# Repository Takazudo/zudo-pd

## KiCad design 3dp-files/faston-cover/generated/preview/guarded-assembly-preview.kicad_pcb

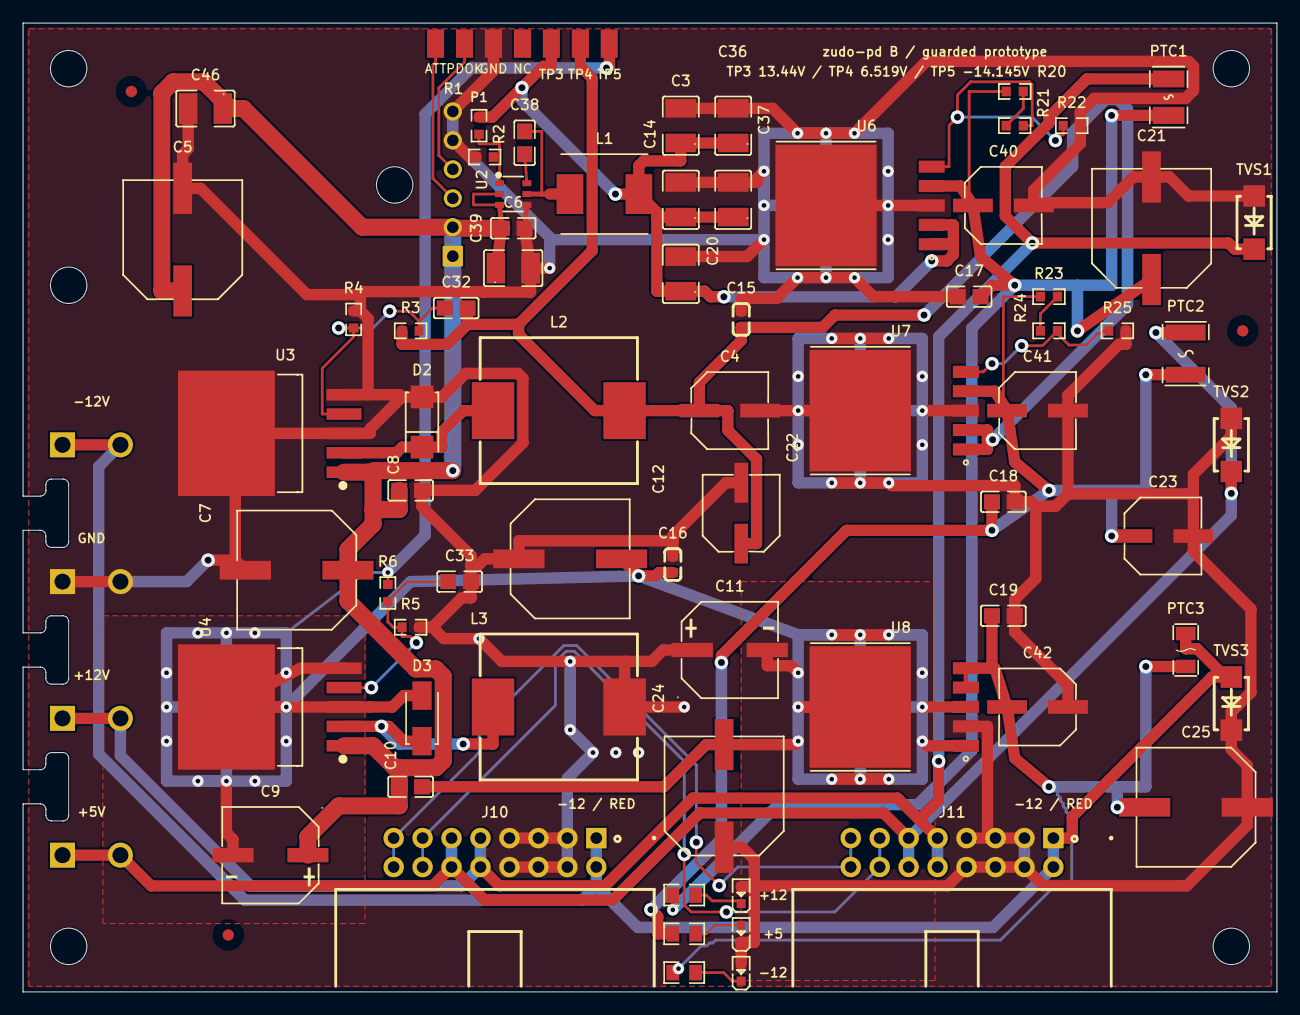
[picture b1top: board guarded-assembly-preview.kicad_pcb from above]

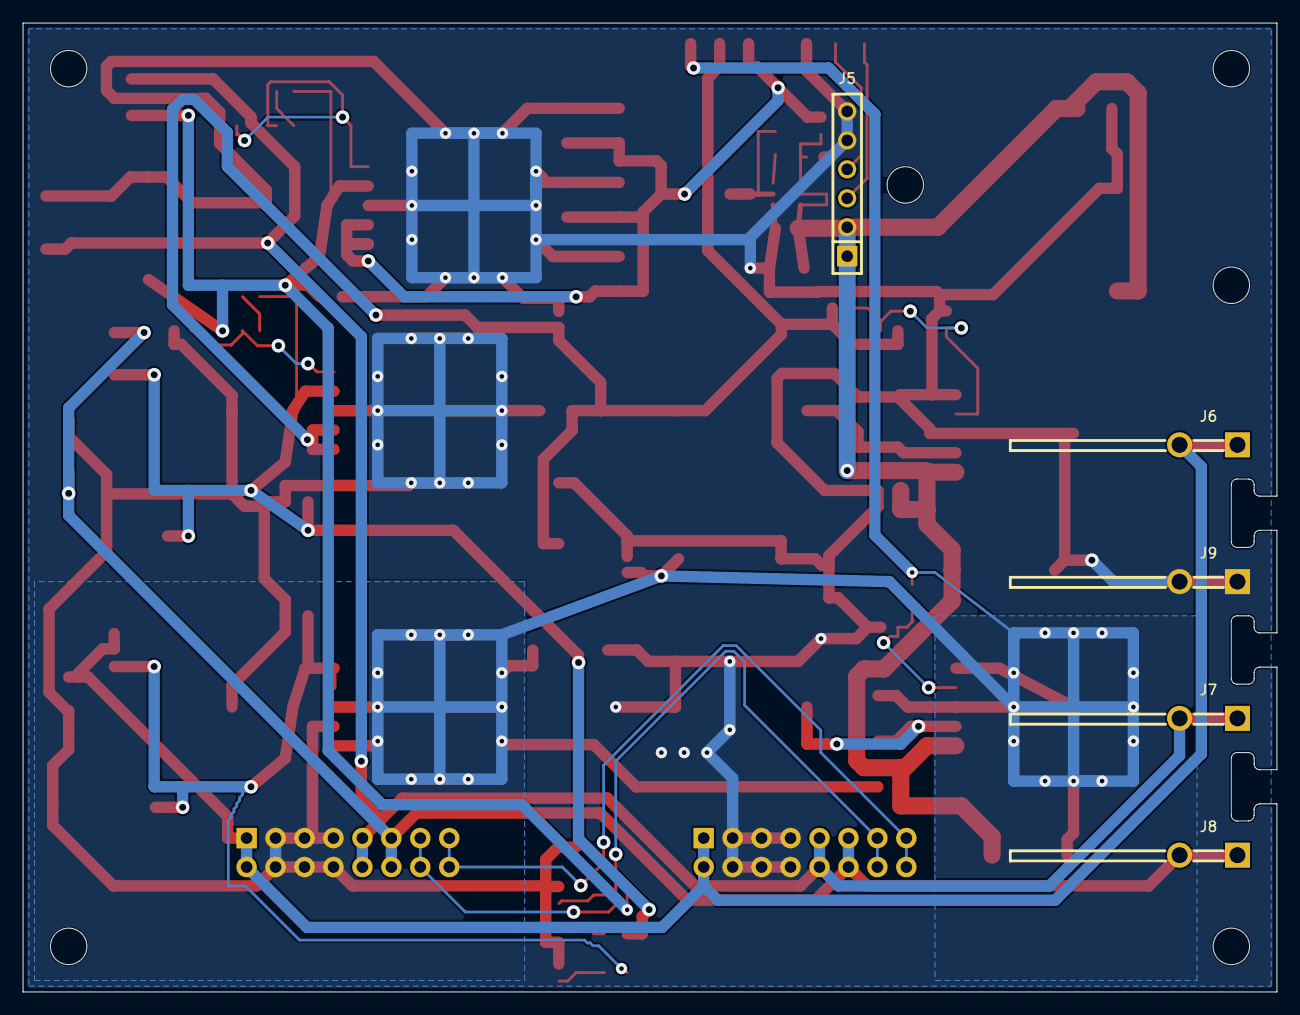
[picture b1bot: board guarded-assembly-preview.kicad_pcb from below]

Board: 2 copper layers, 110.0 x 85.0 mm, 88 parts (5 on the bottom side), 29 nets.

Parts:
C3, C14, C20, C36, C37, C39, C46: 10uF 50V X7R; C1210
C4, C22, C23: 470uF 10V; CAP-SMD_BD6.3-L6.6-W6.6-FD
C5, C7, C12, C21, C24, C25: 470uF 35V; CAP-SMD_BD10.0-L10.3-W10.3-LS11.0-FD
C6, C8, C10, C17, C18, C19, C38: 100nF 50V; C0805
C9: 100uF 50V; CAP-SMD_BD8.0-L8.3-W8.3-LS9.0-FD
C11: 470uF 25V; CAP-SMD_BD8.0-L8.3-W8.3-LS9.0-FD
C15, C16: 470nF; C0603
C32, C33: 22nF; C0805
C40, C41, C42: 47uF 25V polymer; CAP-SMD_BD6.3-L6.6-W6.6-FD
D2: SS34; SMA_L4.3-W2.6-LS5.2-RD
D3: SDT5A60SA-13; SMA_Diodes_SDT5A60SA_C3024223
FID1, FID2, FID3: Fiducial; Fiducial_1mm_Mask2mm
H1, H2, H3, H4, H5, H6: MountingHole_M3
J5: PM254V-11-06-H85; HDR-TH_6P-P2.54-V-F
J6, J7, J8, J9: 63951-1; CONN-TH_1217754-1
J10, J11: DW254P-2X8-L0; IDC-TH_16P-P2.54_321016RG0ABK00A01
L1: 10uH; ASPI-0630LR_L7.5-W6.85
L2, L3: 100uH; IND-SMD_L13.8-W12.8
LED2: Green; LED0603-RD
LED3: Blue; LED0603-RD
LED4: Red; LED0603-RD
MECH_PREVIEW: COVER_AND_PD_REVIEW_ONLY; Mechanical_Preview
P1: ATT/PDOK pads; PogoEdge_BoardB_1x04_P2.54mm
PTC1: SMD1210P150TF/16; F1210
PTC2: mSMD110-33V; F1812
PTC3: BSMD1206-150-16V; F1206
R1: 158k 0.1%; R0603
R2: 10k 0.1%; R0603
R3: 4300R; R0603
R4: 1k; R0603
R5: 10500R; R0603
R6: 1000R; R0603
R7, R8, R9: 1k; R0805
R20: 8200R 0.1%; R0603
R21: 680R 0.1%; R0603
R22, R25: 1000R 0.1%; R0603
R23: 3090R 0.1%; R0603
R24: 33R 0.1%; R0603
TP3: +13.44V; PogoEdge_1x01_1.5x2.5mm
TP4: +6.519V; PogoEdge_1x01_1.5x2.5mm
TP5: -14.145V; PogoEdge_1x01_1.5x2.5mm
TVS1, TVS3: SMAJ15A; D-FLAT_L4.3-W2.6-LS5.3-RD
TVS2: SMAJ6.5A; D-FLAT_L4.3-W2.6-LS5.3-RD
U2: AP63201WU-7; TSOT-23-6_L2.9-W1.6-P0.95-LS2.8-BR
U3, U4: LM2596S-ADJ; TO-263-5_L10.2-W8.9-P1.70-BR
U6, U7: LT1963AEQ#PBF; TO-263-5_L10.6-W9.6-P1.70-LS15.9-BR
U8: LT3015EQ-12#PBF; DD-PAK-5_L10.2-W8.9-P1.70-LS14.0-BR

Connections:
+5V rail: J8.1, J8.2, J10.11, J10.12, J11.11, J11.12, PTC2.2, TVS2.1
+12V rail: J7.1, J7.2, J10.9, J10.10, J11.9, J11.10, PTC1.2, TVS1.1
+15V INPUT: C5.1, C6.1, C7.1, C8.1, C9.1, C10.1, C39.1, C46.1, J5.1, J5.2, U2.2, U2.3, U3.1, U4.1
-12V rail: J6.1, J6.2, J10.1, J10.2, J11.1, J11.2, PTC3.2, TVS3.2
ATT: J5.3, P1.1
CV rail: J10.13, J10.14, J11.13, J11.14
GATE rail: J10.15, J10.16, J11.15, J11.16
GND: C3.2, C4.2, C5.2, C6.2, C7.2, C8.2, C11.1, C12.1, C14.2, C15.2, C16.2, C17.1, C18.2, C19.2, C20.2, C21.2, C22.2, C23.2, C24.1, C25.1, C33.2, C36.2, C37.2, C39.2, C40.2, C41.2, C42.1, C46.2, D2.2, J5.5, J5.6, J9.1, J9.2, J10.3, J10.4, J10.5, J10.6, J10.7, J10.8, J11.3, J11.4, J11.5, J11.6, J11.7, J11.8, L3.2, LED2.2, LED3.1, LED4.2, P1.3, R2.1, R4.2, R5.2, R22.2, R25.2, TVS1.2, TVS2.2, TVS3.1, U2.4, U3.3, U3.5, U3.6, U6.3, U6.6, U7.3, U7.6, U8.2
unnamed: D2.1, L2.1, U3.2
unnamed: D3.1, L3.1, U4.2
unnamed: LED2.1, R7.2
unnamed: LED3.2, R8.2
unnamed: LED4.1, R9.2
unnamed: R1.1, R2.2, U2.1
unnamed: C32.1, R3.2, R4.1, U3.4
unnamed: C33.1, R5.1, R6.1, U4.4
unnamed: C17.2, C21.1, C40.1, PTC1.1, R7.1, R20.1, U6.4
unnamed: C18.1, C23.1, C41.1, PTC2.1, R8.1, R23.1, U7.4
unnamed: C19.1, C25.2, C42.2, PTC3.1, R9.1, U8.4, U8.5
PDOK: J5.4, P1.2
U2_BST: C38.1, U2.6
U2_SW: C38.2, L1.1, U2.5
U6 ADJ: R21.2, R22.1, U6.5
U6 FB upper series: R20.2, R21.1
U7 ADJ: R24.2, R25.1, U7.5
U7 FB upper series: R23.2, R24.1
/DC-DC Conversion/+6.519V PRE: C4.1, C15.1, C22.1, C32.2, L2.2, R3.1, TP4.1, U7.1, U7.2
/DC-DC Conversion/+13.44V PRE: C3.1, C14.1, C20.1, C36.1, C37.1, L1.2, R1.2, TP3.1, U6.1, U6.2
/DC-DC Conversion/-14.145V PRE: C9.2, C10.2, C11.2, C12.2, C16.1, C24.2, D3.2, R6.2, TP5.1, U4.3, U4.5, U4.6, U8.1, U8.3, U8.6

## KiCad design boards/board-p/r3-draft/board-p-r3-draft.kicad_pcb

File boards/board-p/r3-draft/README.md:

# Board P r3 development review

Generated by `scripts/pcb/board-p-r3-draft/annotate-fit.py` from the current routing and native receipts.

**DEVELOPMENT REVIEW — not fabrication/order qualification.** The valid PD20 pair is
`board-p` + `board-b20-draft`. The 20 V / 5 A contract is preserved. Native CAD,
interface/electrical acceptance, supplier preview and measured performance are separate gates.
See [prototype order readiness](../../../manufacturing/prototype-order-readiness.md).

PCB SHA-256: `3cc1affe9901063b3f6a02d5628bd18698304ada89d8e5bfffde3ff600e5782f`.

KiCad 10.0.6 native DRC: **0 errors, 0 unconnected items**. The complete parity findings and warning objects are in [native-drc.json](native-drc.json); their source/tool identity is in [native-drc-receipt.json](native-drc-receipt.json).

| Native warning category | Count |
| --- | ---: |
| `lib_footprint_issues` | 3 |
| `lib_footprint_mismatch` | 3 |
| `silk_over_copper` | 30 |
| `silk_overlap` | 57 |
| `via_dangling` | 2 |

The only retained parity exceptions are the specifically reviewed mechanical-only
MH1–MH3 footprints, excluded from BOM/CPL. Warning classifications and functional
annular-junction details are in [layout-corrections.md](layout-corrections.md).
Warnings are not automatically accepted for manufacturing merely because they are warnings.

## Corrective layout and remaining holds

R1–R4 native geometry is implemented and checked for these PCB bytes. The dated implementation dispositions and remaining process/thermal limits are in [independent-review.md](independent-review.md) and [layout-corrections.md](layout-corrections.md).

- R1: four U2 thermal vias contact 595.369 mm² of connected B.Cu GND.
- R2: four Q1 drain vias contact 22.640 mm² of B.Cu VBUS_OUT.
- R3: three Q3 drain vias contact 3.137 mm² of B.Cu EF_IN.
- R4: C30/C34 pad distances are 2.866/1.602 mm; planar supply paths are 3.237/2.382 mm with 0/1 via transitions. Direct cap-to-return-via tracks are 0.900/0.986 mm.

Via barrels are excluded from planar path length. Filled area is geometry, not an installed thermal resistance or current rating. R1–R3 stencil/via-process approval and the shared land/paste adaptations remain pre-order manufacturing holds. R5 and R7 physical/conditional limitations remain open; no lower current ceiling is adopted.

Functional probe silk uses front contact ordinals and indexed reverse-side role maps, including J3.4 VBUS and J3.5 GND. Q3/D13 reference fields are retained on Fab to expose D5/D8 polarity cues; D5 has one checked printable pin1 marker. The matching artwork-only proof is [probe-silk-check.json](probe-silk-check.json); native DRC status is reported above. Text is 1.0 mm with 0.15 mm strokes and conservative mask-opening clearance ≥0.15 mm. This is a CAD/mask screen; supplier tenting and printed legibility remain unobserved.

## Rebuild and evidence ownership

Use the [owned native workflow](../../../scripts/pcb/board-p-r3-draft/README.md).
The committed `search-two-sided.json` is the placement owner; do not enable
`R3_SEARCH=1` for an ordinary rebuild. Only C30/C34 placement differs from the
November 8 reviewed baseline; footprint identities, outline, connectors and
mounting geometry are checked separately by the native correction verifier.

`pours.json` owns fixed power/ground copper, thermal vias and short regulator
escapes. The current routed artifact contains 579 tracks and
90 routing/fixed vias; the fill stage adds 4
grid stitching vias and 0 island vias. Routing reports
0 open signal connections and 0
detached GND clusters. These are routing results, not substitutes for native DRC.

All sampled power-path cuts have single filled runs of 1.85–4.70 mm.
The 1.82 mm target uses IPC-2221, 1 oz copper and an assumed 20 °C rise; it is
conditioned arithmetic, not a measured 5 A thermal rating. The two-sided build
has 26 bottom-side parts; final pair mechanical evidence is separate.

The default seeds are 12, 14, 16 and 20. Actual completion, selected seed and
fresh-builder/saved-route replay identity are retained in
[native-full-builder-replay-20261110.json](native-full-builder-replay-20261110.json).
The final artwork-only stage replay is recorded separately in
[native-replay.json](native-replay.json); it preserves that checked filled copper
and does not rerun heuristic routing. Stable generated UUIDs and explicit
canonical project copies prevent native object ordering/default-project drift
from silently changing filled copper. A successful replay does not establish
supplier process approval or electrical order readiness.

## Historical findings

The [November 8 independent review](independent-review.md) retains the original
R1–R8 findings and baseline hash, followed by dated corrective dispositions.
Historical phase-13/14/15 DRC and ground-cluster results remain explicitly
historical in `placement-report.json`; they are not reused as current acceptance.
The old top-only heuristic search left 20 parts unplaced in 25 restarts. That
search result is not proof of infeasibility and is not rerun by this correction.

The old r3 + PD15 Board B stack is an invalid pair. Its C3/U3 conflict motivated
the B20 r3 keepout; it does not require redesigning the received S3 Board B.
Historically, C3's 8.3 × 8.3 mm base overlapped that Board B U3 courtyard by
3.31 × 4.05 mm. The 10.2 mm nominal C3 and the old H4.5 model exceeded the
11.1 mm nominal plane gap; the H4.5 value was a model attribute, not a datasheet
fact. The current valid P/B20 pair requires its own fresh datum/assembly evidence.

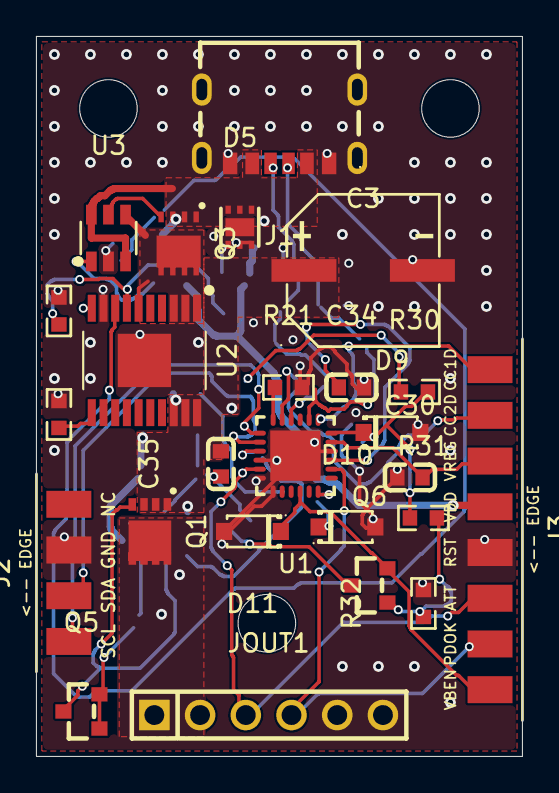
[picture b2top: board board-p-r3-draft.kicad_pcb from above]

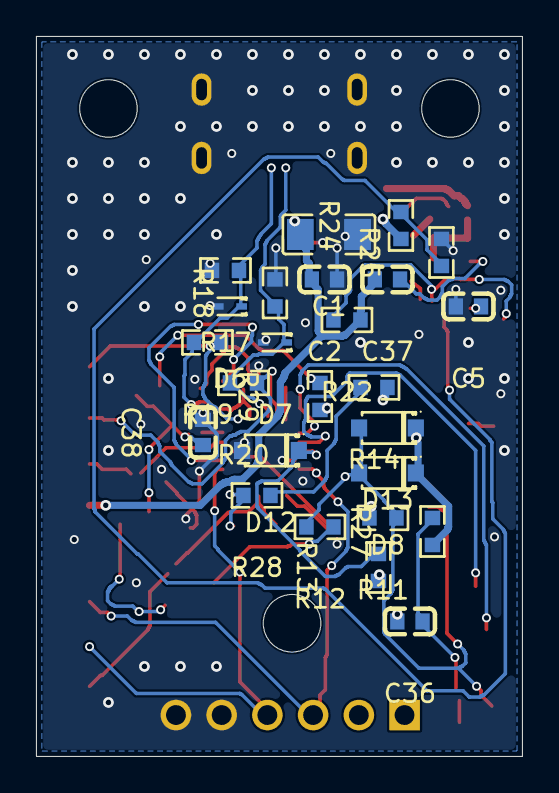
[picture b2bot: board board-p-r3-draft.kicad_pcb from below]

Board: 2 copper layers, 27.0 x 40.0 mm, 53 parts (25 on the bottom side), 32 nets.

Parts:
C1: 10uF/50V; C1206
C2, C5, C35: 100nF/50V; C0603
C3: 100uF 50V; CAP-SMD_BD8.0-L8.3-W8.3-LS9.0-FD
C30, C34, C36, C37, C38: 1uF/50V; C0603
D5: TVS2200DRVR; WSON-6_L2.0-W2.0-P0.65-BL-EP
D6, D7: PESD24VS1UB; SOD-523_L1.2-W0.8-LS1.6-RD
D8, D13: BZT52C11-7-F; SOD-123_L2.8-W1.8-LS3.7-RD
D9, D11, D12: BZT52C18-7-F; SOD-123_L2.8-W1.8-LS3.7-RD
D10: BZT52C20-7-F; SOD-123_L2.8-W1.8-LS3.7-RD
J1: TYPE-C-31-M-17; USB-C-SMD_10P-P1.00-L6.8-W8.9
J2: PogoPad_1x4_NVM_I2C; PogoPad_1x04_P2.54mm
J3: PogoPad_1x8_Debug; PogoPad_1x08_P2.54mm
JOUT1: 2.54mm 1x6 male; HDR-TH_6P-P2.54-V-M
MH1, MH2, MH3: MountingHole_3.2mm_M3
Q1: DMP3036SFG-7; PowerDI3333-8_DMP3036SFG
Q3: CSD18543Q3A; VSON-8_L3.3-W3.3-P0.65_CSD18543Q3A
Q5, Q6: BSS138-7-F; SOT-23_DIODES-DS30144-SUGGESTED
R11, R27: 150k; R0603
R12, R13: 4.7k; R0603
R14, R28, R29: 1k; R0603
R17, R18: 5.1k; R0603
R19, R20, R21: 0R; R0603
R22: 11.5k 0.1%; R0603
R23, R26: 4.02k 0.1%; R0603
R24: 174k 0.1%; R0603
R25: 10k 0.1%; R0603
R30: 470R; R0603
R31, R32: 100k; R0603
U1: STUSB4500QTR; QFN-24_L4.0-W4.0-P0.50-BL-EP2.8
U2: TPS16630PWPR; HTSSOP-20_PWP0020T_P0.65_EP2.96_TI-DRAFT
U3: LM74700QDBVRQ1; SOT-23-6_TI-DBV0006A

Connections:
ATT: J3.6, JOUT1.3, U1.11
CC1: D6.1, J1.3, R17.1, R19.2, U1.2
CC1DB: J3.1, R19.1, U1.1
CC2: D7.1, J1.4, R18.1, R20.2, U1.4
CC2DB: J3.2, R20.1, U1.5
DISCH: D12.1, R13.2, U1.9
EF_DVDT: C5.1, U2.10
EF_GATE: Q3.4, U3.5
EF_ILIM: R26.1, U2.11
EF_IN: Q3.5, Q3.6, Q3.7, Q3.8, Q3.9, U2.1, U2.2, U2.3, U2.6, U3.4
EF_OVP: R24.2, R25.1, U2.8
EF_UVLO: R22.2, R23.1, U2.7
EF_VCAP: C37.1, U3.1
GND: C1.1, C2.1, C3.2, C5.2, C30.1, C34.2, C38.2, D5.1, D5.2, D5.3, D5.7, D6.2, D7.2, D9.2, D10.2, D11.2, D12.2, J1.0, J1.1, J1.6, J2.3, J3.5, JOUT1.5, JOUT1.6, R17.2, R18.2, R21.2, R23.2, R25.2, R26.2, R32.2, U1.10, U1.12, U1.13, U1.22, U1.25, U2.9, U2.21, U3.2
PDOK: J3.7, JOUT1.4, U1.20
Q1_G: C35.1, D8.2, D13.2, Q1.4, Q5.3, R11.1, R12.2
Q1_MX: C36.1, Q5.1, Q5.2, R27.2
RESET: R21.1, U1.6
SCL: J2.1, U1.7
SDA: J2.2, U1.8
VBEN: Q6.3, R12.1
VBEN_PIN: D11.1, J3.8, Q6.2, U1.16
VBUS_DISCH_R: R14.2, R28.1
VBUS_IN: C1.2, C2.2, C37.2, D5.4, D5.5, D5.6, J1.2, J1.5, J3.4, Q3.1, Q3.2, Q3.3, R22.1, R24.1, U3.3, U3.6
VBUS_OUT: C36.2, JOUT1.1, JOUT1.2, Q1.5, Q1.6, Q1.7, Q1.8, Q1.9, R13.1
VBUS_P: C3.1, C35.2, D8.1, D13.1, Q1.1, Q1.2, Q1.3, R11.2, R14.1, R27.1, R29.1, U2.18, U2.19, U2.20
VBUS_VS_DISCH: D10.1, R28.2, U1.18
VDD_LOC: C38.1, D9.1, R30.2, R31.1, U1.24
VDD_MID: R29.2, R30.1
VG_LOC: Q6.1, R31.2, R32.1
VREG_1V2: C34.1, U1.21
VREG_2V7: C30.2, J3.3, U1.23

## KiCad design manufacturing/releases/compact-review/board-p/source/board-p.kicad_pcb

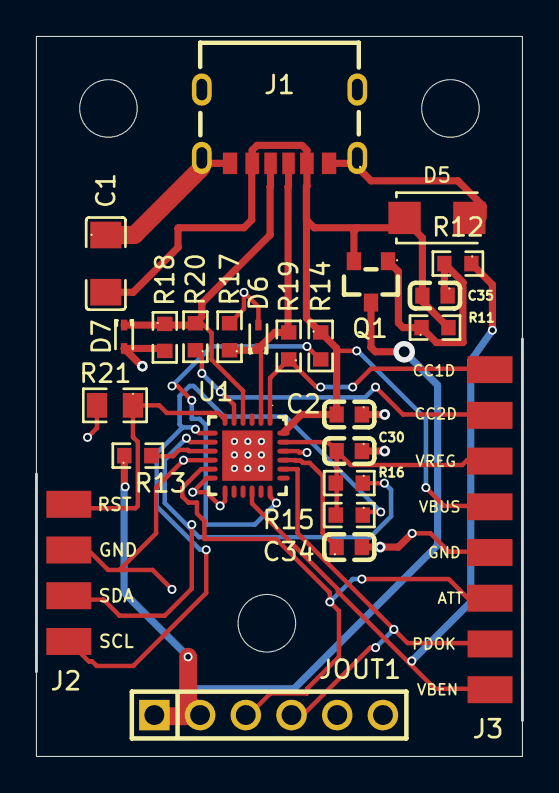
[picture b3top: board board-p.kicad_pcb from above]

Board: 2 copper layers, 27.0 x 40.0 mm, 28 parts (0 on the bottom side), 18 nets.

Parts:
C1: 10uF/50V; C1206
C2, C35: 100nF/50V; C0603
C30, C34: 1uF/50V; C0603
D5: SMAJ16A-E3/61; SMA_Vishay_SMAJ16A_C968650
D6, D7: PESD24VS1UB; SOD-523_L1.2-W0.8-LS1.6-RD
J1: TYPE-C-31-M-17; USB-C-SMD_10P-P1.00-L6.8-W8.9
J2: PogoPad_1x4_NVM_I2C; PogoPad_1x04_P2.54mm
J3: PogoPad_1x8_Debug; PogoPad_1x08_P2.54mm
JOUT1: 2.54mm 1x6 male; HDR-TH_6P-P2.54-V-M
MH1, MH2, MH3: MountingHole_3.2mm_M3
Q1: AO3401A; SOT-23_L2.9-W1.3-P1.90-LS2.4-BR
R11: 100k; R0603
R12: 150k; R0603
R13, R14: 470R; R0603
R15, R16: 4.7k; R0603
R17, R18: 5.1k; R0603
R19, R20: 0R; R0603
R21: 10k; R0805
U1: STUSB4500QTR; QFN-24_L4.0-W4.0-P0.50-BL-EP2.8

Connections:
ATT: J3.6, JOUT1.3, U1.11 (ATTACH)
CC1: D6.1 (C), J1.3 (A5), R17.1, R19.2, U1.2 (CC1)
CC1DB: J3.1, R19.1, U1.1 (CC1DB)
CC2: D7.1 (C), J1.4 (B5), R18.1, R20.2, U1.4 (CC2)
CC2DB: J3.2, R20.1, U1.5 (CC2DB)
DISCH: R13.2, U1.9 (DISCH)
GND: C1.1, C2.1, C30.1, C34.2, D5.2, D6.2 (A), D7.2 (A), J1.0, J1.1 (B12), J1.6 (A12), J2.3, J3.5, JOUT1.5, JOUT1.6, R17.2, R18.2, R21.2, U1.10 (GND), U1.12 (ADDR0), U1.13 (ADDR1), U1.22 (VSYS), U1.25 (EP)
PDOK: J3.7, JOUT1.4, U1.20 (POWER_OK2)
Q1_G: C35.1, Q1.1 (G), R11.1, R12.2
RESET: J2.4, R21.1, U1.6 (RESET)
SCL: J2.1, R15.1, U1.7 (SCL)
SDA: J2.2, R16.1, U1.8 (SDA)
VBEN: J3.8, R12.1, U1.16 (VBUS_EN_SNK)
VBUS_IN: C1.2, C2.2, C35.2, D5.1, J1.2 (B9), J1.5 (A9), J3.4, Q1.2 (S), R11.2, R14.1, U1.24 (VDD)
VBUS_OUT: JOUT1.1, JOUT1.2, Q1.3 (D), R13.1
VBUS_VS_DISCH: R14.2, U1.18 (VBUS_VS_DISCH)
VREG_1V2: C34.1, U1.21 (VREG_1V2)
VREG_2V7: C30.2, J3.3, R15.2, R16.2, U1.23 (VREG_2V7)
